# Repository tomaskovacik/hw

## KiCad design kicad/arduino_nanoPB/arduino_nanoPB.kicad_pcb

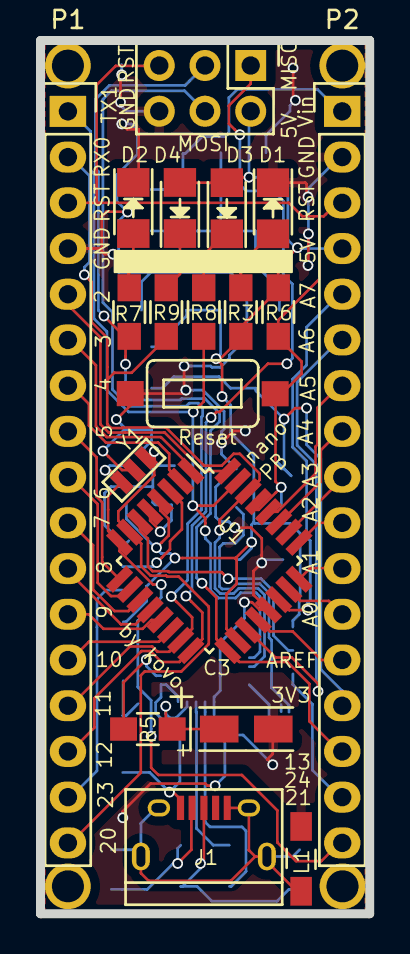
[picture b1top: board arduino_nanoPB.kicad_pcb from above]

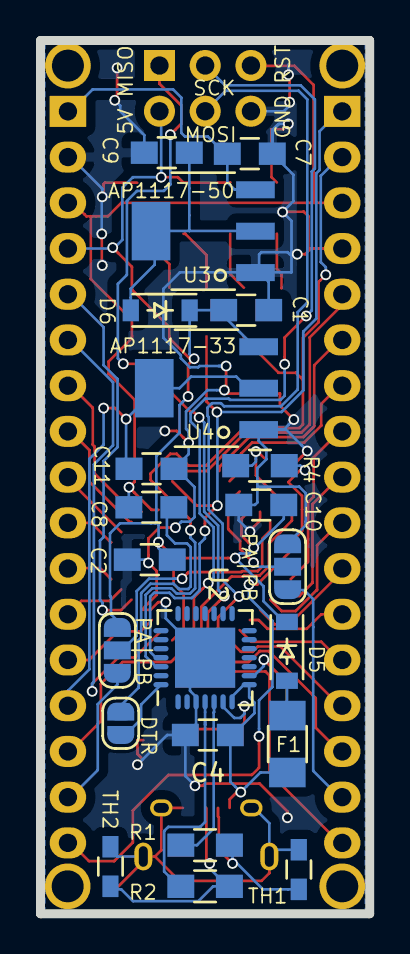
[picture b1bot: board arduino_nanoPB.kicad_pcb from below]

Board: 2 copper layers, 18.3 x 48.5 mm, 45 parts (22 on the bottom side), 50 nets.

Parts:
C1, C2, C4, C7, C8, C9, C10, C11: 0.1m; C_0805_HandSoldering
C3: 1u; TantalC_SizeA_EIA-3216_Wave
D1: Green RED; LED-1206
D2: Red LED; LED-1206
D3, D4: Yellow LED; LED-1206
D5, D6: MBR120; SOD-123
F1: Fuse; Fuse_SMD1206_Wave
J1: USB_B_Micro; USB_Micro-B
JP1, JP2: Jumper_3_Open; SolderJumper-3_P1.3mm_Open_RoundedPad1.0x1.5mm_NumberLabels
JP3: SolderJumper_2_Bridged; SolderJumper-2_P1.3mm_Open_RoundedPad1.0x1.5mm
L1: L; Choke_SMD_1206_Standard
P1: Digital; Pin_Header_Straight_1x17
P2: Analog; Pin_Header_Straight_1x17
P3, P4, P5, P6: CONN_01X01; 1pin_Nano
P7: CONN_6; Pin_Header_Straight_2x03
R1, R2: 20; R_0805_HandSoldering
R3, R7, R8, R9: 1k; R_0805_HandSoldering
R4: 1M; R_0805_HandSoldering
R5, R6: 10k; R_0805_HandSoldering
SW1: SW_PUSH; 3x6x2.5mm_tact_switch
TH1, TH2: CG0603MLC-05E; R_0603_HandSoldering
U1: ATMEGA328PB-AU; TQFP-32_7x7mm_Pitch0.8mm
U2: CP2102N-A01-GQFN28; QFN-28-1EP_5x5mm_Pitch0.5mm
U3: AP1117-50; AB2_SOT223
U4: AP1117-33; AB2_SOT223
Y1: Resonator; MURATA_CSTCE_V53

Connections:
3V3: C11.1, P2.14, U4.2
+5V: C1.2, C2.2, C10.1, D3.2, D4.2, D5.1, D6.1, JP2.3, P2.4, P7.2, R3.1, R6.1, U1.4, U1.18, U4.3
/0(Rx): P1.2, R9.1, U1.30, U2.26
/1(Tx): P1.1, R8.1, U1.31, U2.25
/2: P1.5, U1.32
/3(**): P1.6, U1.1
/4: P1.7, U1.2
/5(**): P1.8, U1.9
/6(**): P1.9, U1.10
/7: P1.10, U1.11
/8: P1.11, U1.12
/9(**): P1.12, U1.13
/10(**/SS): P1.13, U1.14
/11(**/MOSI): P1.14, P7.4, U1.15
/12(MISO): P1.15, P7.1, U1.16
/13(SCK): P2.15, P7.3, R7.1, U1.17
/20: P1.17, R4.1, U1.7, Y1.3
/21: P2.17, R4.2, U1.8, Y1.1
/#RST: R5.1, U2.9
/A0: P2.12, U1.23
/A1: P2.11, U1.24
/A2: P2.10, U1.25
/A3: P2.9, U1.26
/A4: P2.8, U1.27
/A5: P2.7, U1.28
/A6: P2.6, U1.19
/A7: P2.5, U1.22
/AREF: P2.13, U1.20
/D23: JP1.1, P1.16
/D24: JP2.1, P2.16
/D+: J1.3, R2.2, TH2.1
/D-: J1.2, R1.2, TH1.1
/DD+: R2.1, U2.4
/DD-: R1.1, U2.5
/DTR: JP3.2, U2.28
/MEGA3: JP1.2, U1.3
/MEGA6: JP2.2, U1.6
/Reset: C8.1, P1.3, P2.3, P7.5, R6.2, SW1.1, U1.29
/VBUS: C4.1, F1.2, J1.1, U2.7, U2.8
/Vin: C7.1, P2.1, U3.3
GND: C1.1, C2.1, C3.2, C4.2, C7.2, C9.2, C10.2, C11.2, D1.1, D2.1, JP1.3, L1.1, P1.4, P2.2, P7.6, SW1.2, U1.5, U1.21, U2.3, U2.29, U3.1, U4.1, Y1.2
GNDPWR: J1.5, J1.6, L1.2, TH1.2, TH2.2
unnamed: C3.1, R5.2, U2.6
unnamed: C8.2, JP3.1
unnamed: C9.1, D6.2, U3.2
unnamed: D1.2, R3.2
unnamed: D2.2, R7.2
unnamed: D3.1, R8.2
unnamed: D4.1, R9.2
unnamed: D5.2, F1.1

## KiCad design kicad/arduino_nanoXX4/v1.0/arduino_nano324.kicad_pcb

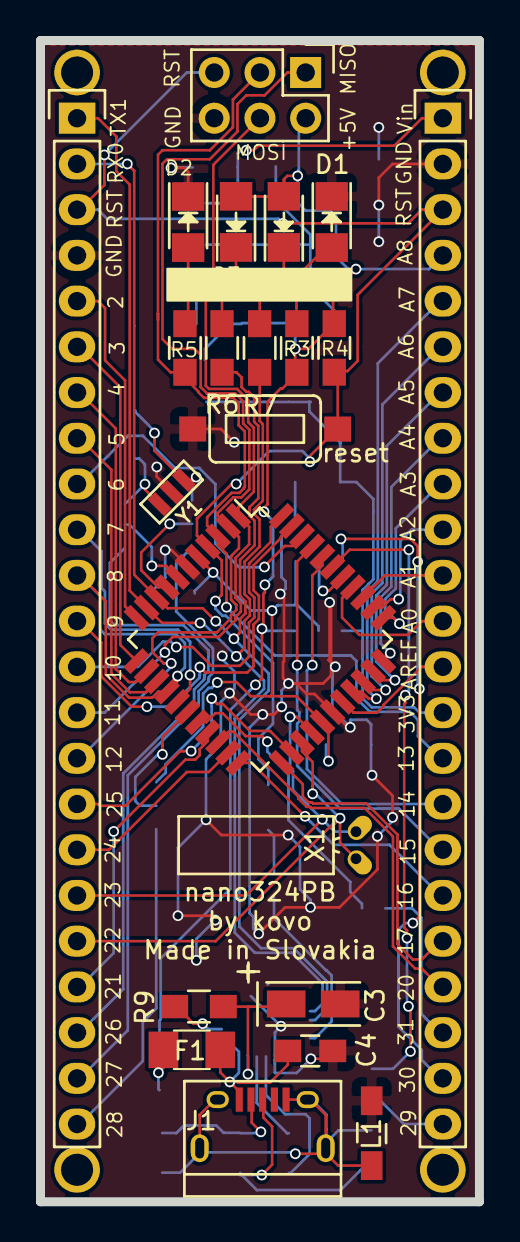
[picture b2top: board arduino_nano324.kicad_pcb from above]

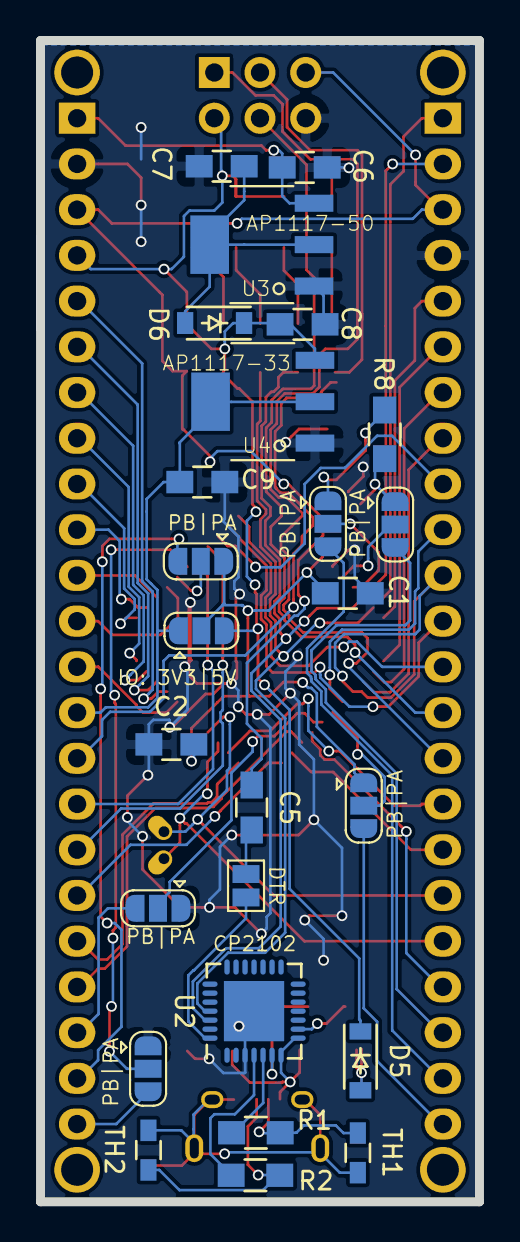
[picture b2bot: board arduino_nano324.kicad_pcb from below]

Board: 2 copper layers, 24.4 x 64.5 mm, 51 parts (25 on the bottom side), 69 nets.

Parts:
C1, C2, C4, C5, C6, C7, C8, C9: 0.1m; C_0805_HandSoldering
C3: 1u; TantalC_SizeA_EIA-3216_Wave
D1: GRED; LED-1206
D2: GLED; LED-1206
D3, D4: YLED; LED-1206
D5, D6: MBR120; SOD-123
F1: Fuse; Fuse_SMD1206_Wave
J1: USB_B_Micro; USB_Micro-B
JP1, JP2, JP3, JP4, JP5, JP6: Jumper_3_Open; SolderJumper-3_P1.3mm_Open_RoundedPad1.0x1.5mm
JP7: VIO; SolderJumper-3_P1.3mm_Open_RoundedPad1.0x1.5mm
JP9: Jumper; SolderJumper-2_P1.3mm_Open_Pad1.0x1.5mm
L1: ferite_bead; Choke_SMD_1206_Standard
P1: Digital; Pin_Header_Straight_1x23
P2: Analog; Pin_Header_Straight_1x23
P3, P4, P5, P6: CONN_01X01; 1pin_Nano
P7: CONN_6; Pin_Header_Straight_2x03
R1, R2: 22; R_0805_HandSoldering
R3, R5, R6, R7: 1k; R_0805_HandSoldering
R4, R9: 10k; R_0805_HandSoldering
R8: 1M; R_0805_HandSoldering
SW1: SW_PUSH; 3x6x2.5mm_tact_switch
TH1, TH2: MLC-05E; R_0603_HandSoldering
U1: ATMEGA324PB-AU; TQFP-44_10x10mm_Pitch0.8mm
U2: CP2102N-A01-GQFN28; QFN-28-1EP_5x5mm_Pitch0.5mm
U3: AP1117-50; AB2_SOT223
U4: AP1117-33; AB2_SOT223
X1: CRYSTAL; Crystal_Round_Horizontal_3mm_BigPad
Y1: 16Mhz; MURATA_CSTCE_V53

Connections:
3V3: C9.1, JP7.1, P2.14, U4.2
+5V: C8.1, D3.2, D4.2, D5.1, D6.1, JP7.3, P2.4, P7.2, R3.1, R4.1, U4.3
/0(Rx): P1.2, R6.1, U1.9, U2.26
/1(Tx): P1.1, R7.1, U1.10, U2.25
/2: P1.5, U1.11
/3(**): P1.6, U1.12
/4: P1.7, U1.13
/5(**): P1.8, U1.14
/6(**): P1.9, U1.42
/7: JP1.2, U1.7
/8: JP2.2, U1.8
/9(**): P1.12, U1.43
/10(**/SS): P1.13, U1.44
/11(**/MOSI): P1.14, P7.4, U1.1
/12(MISO): P1.15, P7.1, U1.2
/13(SCK): P2.15, P7.3, R5.1, U1.3
/17: JP3.2, U1.17
/18: JP4.2, U1.18
/38: JP5.2, U1.38
/39: JP6.2, U1.39
/#RST: R9.1, U2.9
/A0: P2.12, U1.37
/A1: P2.11, U1.36
/A2: P2.10, U1.35
/A3: P2.9, U1.34
/A4: P2.8, U1.33
/A5: P2.7, U1.32
/A6: P2.6, U1.31
/A7: P2.5, U1.30
/AREF: P2.13, U1.29
/D7: P1.10, U1.16
/D8: P1.11, U1.15
/D14: P2.16, U1.40
/D15: P2.17, U1.41
/D16: P2.18, U1.22
/D17: P2.19, U1.23
/D20: P2.20, U1.20
/D21: P1.20, U1.19
/D22: P1.19, U1.25, X1.1
/D23: P1.18, U1.26, X1.2
/D32: P1.17, U1.21
/D33: P1.16, U1.24
/D34: JP1.3, P1.21
/D35: JP2.3, P1.22
/D36: JP3.3, P1.23
/D37: JP4.3, P2.21
/D39: JP5.3, P2.22
/D40: JP6.3, P2.23
/D+: J1.3, R2.2, TH2.1
/D-: J1.2, R1.2, TH1.1
/DD+: R2.1, U2.4
/DD-: R1.1, U2.5
/DTR: JP9.2, U2.28
/Reset: C5.1, P1.3, P2.3, P7.5, R4.2, SW1.1, U1.4
/VBUS: C4.1, F1.2, J1.1, U2.7, U2.8
/Vin: C6.1, P2.1, U3.3
/XTAL1: JP2.1, R8.1, Y1.3
/XTAL2: JP1.1, R8.2, Y1.1
GND: C1.1, C2.1, C3.2, C4.2, C6.2, C7.2, C8.2, C9.2, D1.1, D2.1, JP4.1, JP6.1, L1.1, P1.4, P2.2, P7.6, SW1.2, U1.6, U1.28, U2.3, U2.29, U3.1, U4.1, Y1.2
GNDPWR: J1.5, J1.6, L1.2, TH1.2, TH2.2
unnamed: C3.1, R9.2, U2.6
unnamed: C5.2, JP9.1
unnamed: C7.1, D6.2, U3.2
unnamed: D1.2, R3.2
unnamed: D2.2, R5.2
unnamed: D3.1, R6.2
unnamed: D4.1, R7.2
unnamed: D5.2, F1.1
VCC: C1.2, C2.2, JP3.1, JP5.1, JP7.2, U1.5, U1.27

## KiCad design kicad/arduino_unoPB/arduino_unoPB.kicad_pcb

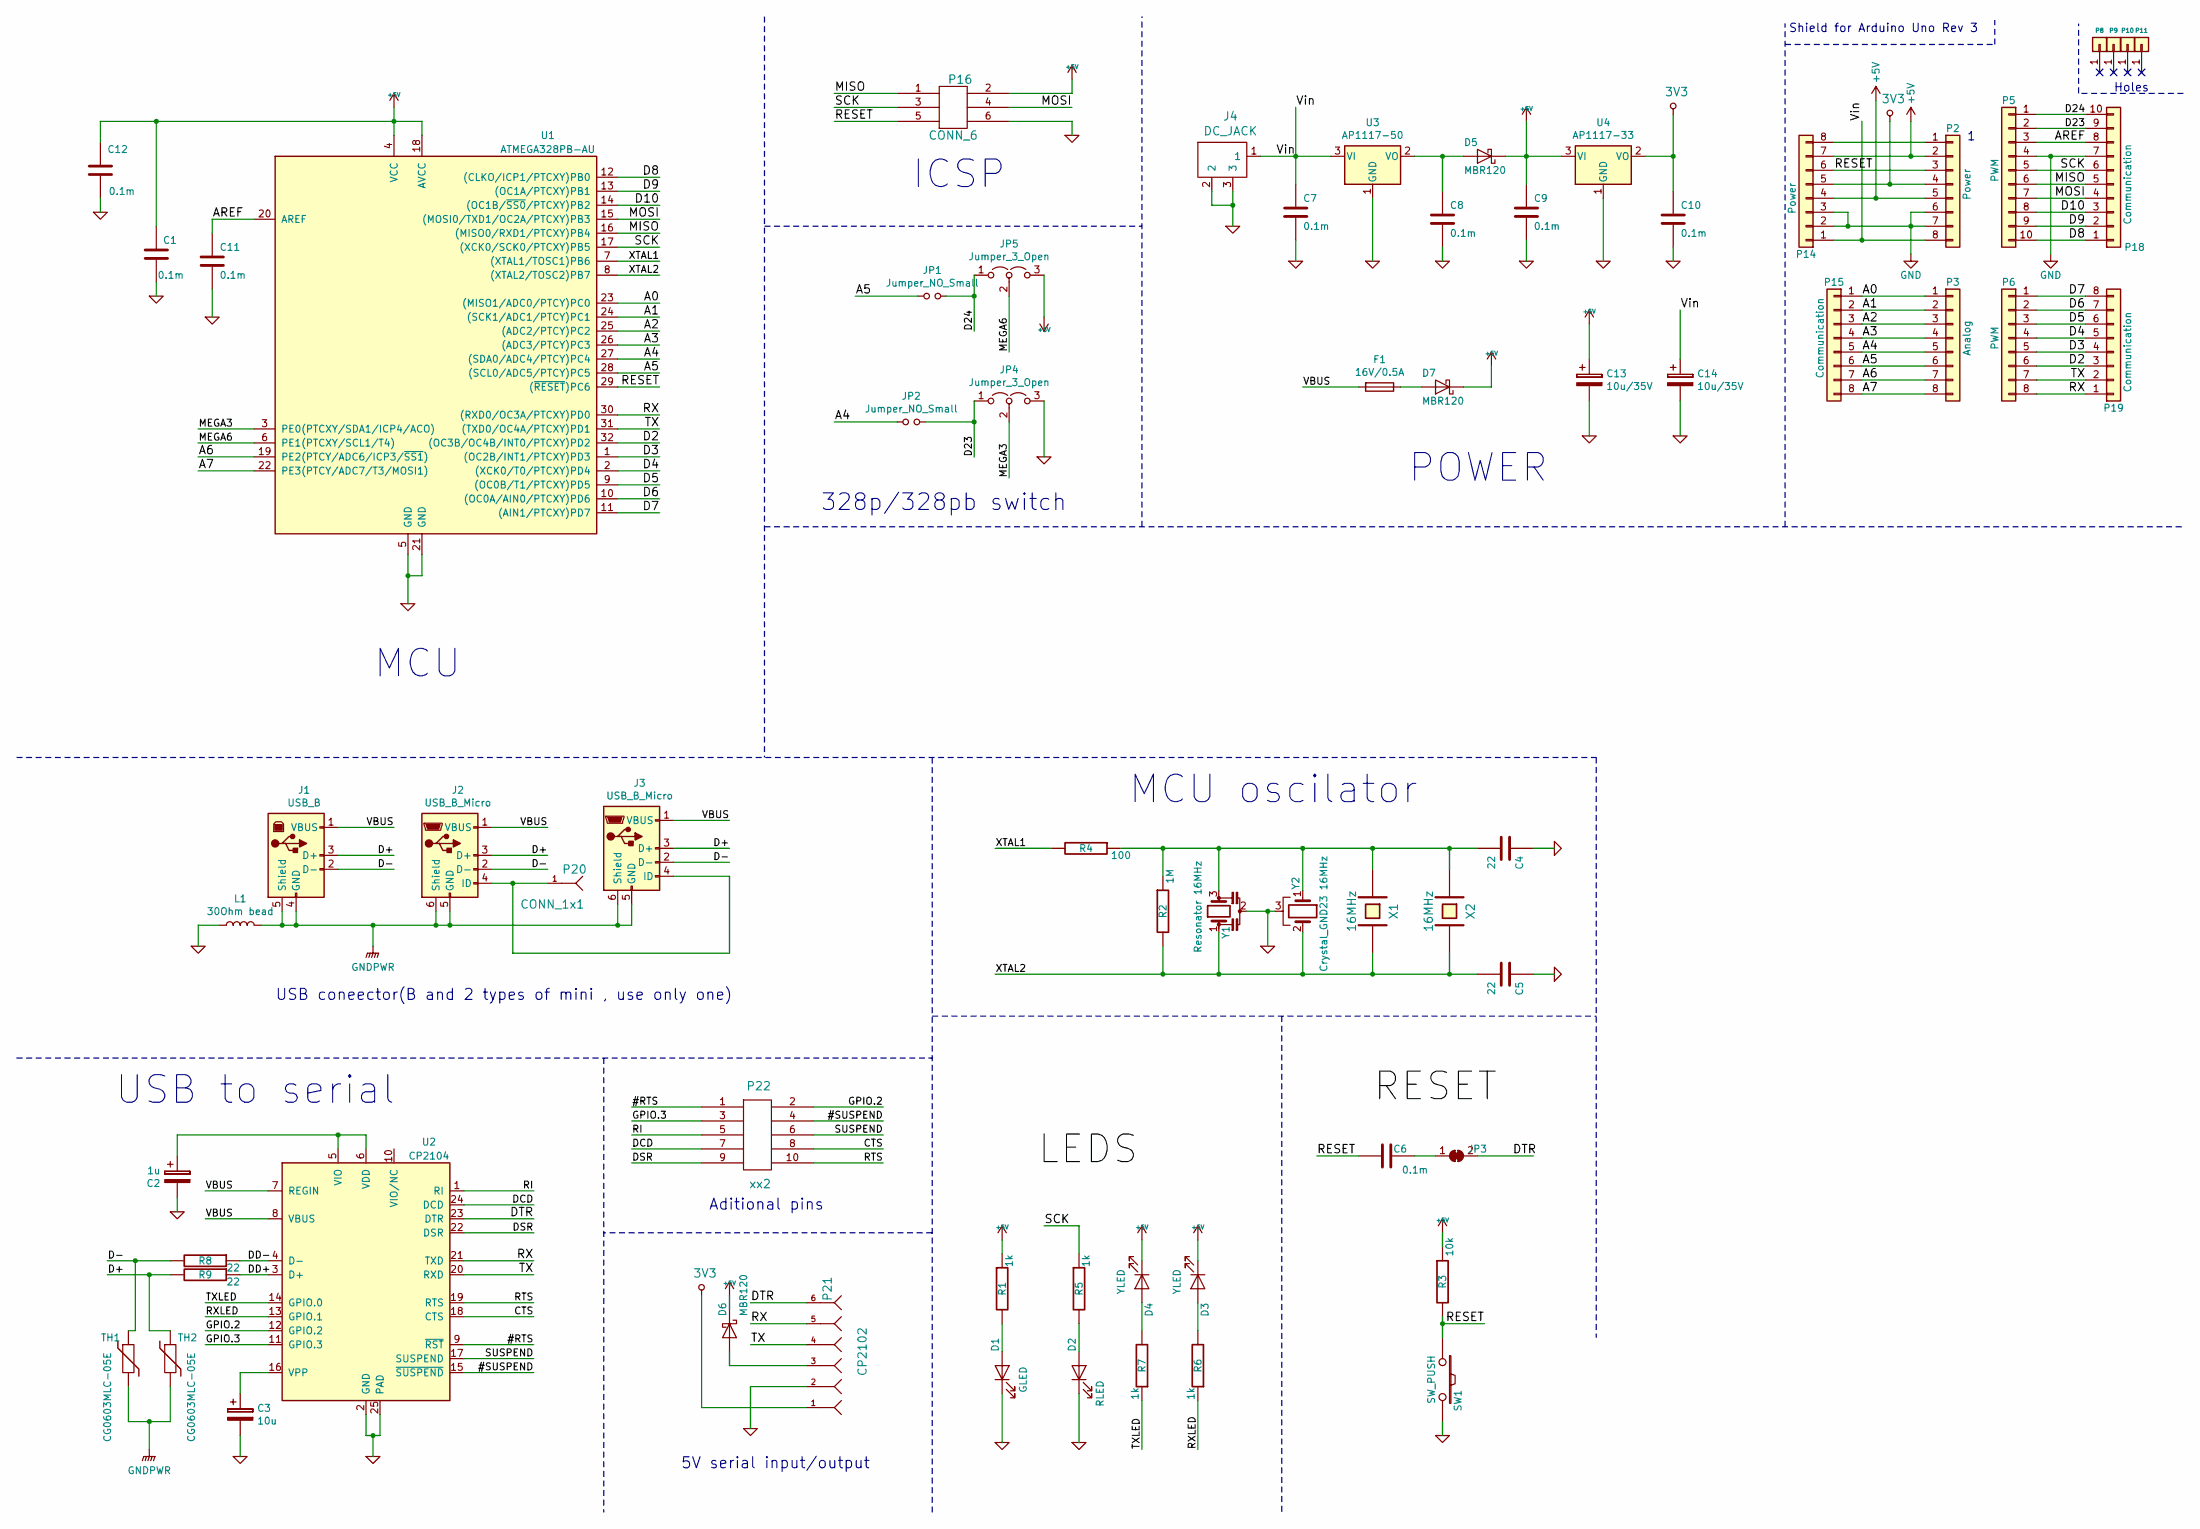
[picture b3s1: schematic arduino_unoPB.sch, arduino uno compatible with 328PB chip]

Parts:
C1, C6, C7, C8, C9, C10, C11, C12: 0.1m; C_0805_HandSoldering
C2: 1u; TantalC_SizeA_EIA-3216_Wave
C3: 10u; TantalC_SizeA_EIA-3216_Wave
C4, C5: 22; C_0805_HandSoldering
C13, C14: 10u/35V; TantalC_SizeD_EIA-7343_Wave
D1: GLED; LED-1206
D2: RLED; LED-1206
D3, D4: YLED; LED-1206
D5, D6, D7: MBR120; SOD-123
F1: 16V/0.5A; Fuse_SMD1206_Wave
J1: USB_B
J2: USB_B_Micro; USB_Micro-B
J3: USB_B_Micro; AB2_USB_MICRO_SMD
J4: DC_JACK; JACK_ALIM
JP1, JP2: Jumper_NO_Small; SolderJumper-2_P1.3mm_Open_RoundedPad1.0x1.5mm
JP3: SolderJumper_2_Bridged; SolderJumper-2_P1.3mm_Bridged_RoundedPad1.0x1.5mm
JP4, JP5: Jumper_3_Open; SolderJumper-3_P1.3mm_Open_RoundedPad1.0x1.5mm_NumberLabels
L1: 30Ohm bead; Choke_SMD_1206_Standard
P2, P14: Power; Pin_Header_Straight_1x08
P3: Analog; Pin_Header_Straight_1x08
P5: PWM; Pin_Header_Straight_1x10
P6: PWM; Pin_Header_Straight_1x08
P8, P9, P10, P11: CONN_01X01; Arduino_1pin
P15, P19: Communication; Pin_Header_Straight_1x08
P16: CONN_6; Pin_Header_Straight_2x03
P18: Communication; Pin_Header_Straight_1x10
P20: CONN_1x1; Pin_Header_Straight_1x01
P21: CP2102; Pin_Header_Straight_1x06
P22: xx2; Pin_Header_Straight_2x05
R1, R5, R6, R7: 1k; R_0805_HandSoldering
R2: 1M; R_0805_HandSoldering
R3: 10k; R_0805_HandSoldering
R4: 100; R_0805_HandSoldering
R8, R9: 22; R_0805_HandSoldering
SW1: SW_PUSH; 3x6x2.5mm_tact_switch
TH1, TH2: CG0603MLC-05E; R_0603_HandSoldering
U1: ATMEGA328PB-AU; TQFP-32_7x7mm_Pitch0.8mm
U2: CP2104; QFN-24-1EP_4x4mm_Pitch0.5mm
U3: AP1117-50; AB2_SOT223
U4: AP1117-33; AB2_SOT223
X1: 16MHz; Crystal_HC49-U_Vertical
X2: 16MHz; Q_49U3HMS
Y1: Resonator 16MHz; MURATA_CSTCE_V53
Y2: Crystal_GND23 16MHz; CRYSTAL_3225

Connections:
3V3: C10.1, P2.4, P14.5, P21.1, U4.2 (VO)
+5V: C1.2, C9.1, C12.2, C13.1, D3.1 (K), D4.1 (K), D5.1 (K), D6.1 (K), D7.1 (K), JP5.3 (B), P2.2, P2.5, P14.4, P14.7, P16.2, R1.1, R3.1, U1.4 (VCC), U1.18 (AVCC), U4.3 (VI)
/#RTS: P22.1, U2.9 (~RST)
/#SUSPEND: P22.4, U2.15 (~SUSPEND)
/A0: P3.1, P15.1, U1.23 ((MISO1/ADC0/PTCY)PC0)
/A1: P3.2, P15.2, U1.24 ((SCK1/ADC1/PTCY)PC1)
/A2: P3.3, P15.3, U1.25 ((ADC2/PTCY)PC2)
/A3: P3.4, P15.4, U1.26 ((ADC3/PTCY)PC3)
/A4: JP2.1, P3.5, P15.5, U1.27 ((SDA0/ADC4/PTCY)PC4)
/A5: JP1.1, P3.6, P15.6, U1.28 ((SCL0/ADC5/PTCY)PC5)
/A6: P3.7, P15.7, U1.19 (PE2(PTCY/ADC6/ICP3/~SS1~))
/A7: P3.8, P15.8, U1.22 (PE3(PTCY/ADC7/T3/MOSI1))
/AREF: C11.1, P5.3, P18.8, U1.20 (AREF)
/CTS: P22.8, U2.18 (CTS)
/D2: P6.6, P19.3, U1.32 ((OC3B/OC4B/INT0/PTCXY)PD2)
/D3: P6.5, P19.4, U1.1 ((OC2B/INT1/PTCXY)PD3)
/D4: P6.4, P19.5, U1.2 ((XCK0/T0/PTCXY)PD4)
/D5: P6.3, P19.6, U1.9 ((OC0B/T1/PTCXY)PD5)
/D6: P6.2, P19.7, U1.10 ((OC0A/AIN0/PTCXY)PD6)
/D7: P6.1, P19.8, U1.11 ((AIN1/PTCXY)PD7)
/D8: P5.10, P18.1, U1.12 ((CLKO/ICP1/PTCXY)PB0)
/D9: P5.9, P18.2, U1.13 ((OC1A/PTCXY)PB1)
/D10: P5.8, P18.3, U1.14 ((OC1B/~SS0~/PTCXY)PB2)
/D23: JP2.2, JP4.1 (A), P5.2, P18.9
/D24: JP1.2, JP5.1 (A), P5.1, P18.10
/D+: J1.3 (D+), J2.3 (D+), J3.3 (D+), R9.2, TH2.1
/D-: J1.2 (D-), J2.2 (D-), J3.2 (D-), R8.2, TH1.1
/DCD: P22.7, U2.24 (DCD)
/DD+: R9.1, U2.3 (D+)
/DD-: R8.1, U2.4 (D-)
/DSR: P22.9, U2.22 (DSR)
/DTR: JP3.2 (B), P21.6, U2.23 (DTR)
/GPIO.2: P22.2, U2.12 (GPIO.2)
/GPIO.3: P22.3, U2.11 (GPIO.3)
/MEGA3: JP4.2 (C), U1.3 (PE0(PTCXY/SDA1/ICP4/ACO))
/MEGA6: JP5.2 (C), U1.6 (PE1(PTCXY/SCL1/T4))
/MISO: P5.6, P16.1, P18.5, U1.16 ((MISO0/RXD1/PTCXY)PB4)
/MOSI: P5.7, P16.4, P18.4, U1.15 ((MOSI0/TXD1/OC2A/PTCXY)PB3)
/RESET: C6.1, P2.3, P14.6, P16.5, R3.2, SW1.1, U1.29 ((~RESET~)PC6)
/RI: P22.5, U2.1 (RI)
/RTS: P22.10, U2.19 (RTS)
/RX: P6.8, P19.1, P21.5, U1.30 ((RXD0/OC3A/PTCXY)PD0), U2.21 (TXD)
/RXLED: R6.1, U2.13 (GPIO.1)
/SCK: P5.5, P16.3, P18.6, R5.1, U1.17 ((XCK0/SCK0/PTCXY)PB5)
/SUSPEND: P22.6, U2.17 (SUSPEND)
/TX: P6.7, P19.2, P21.4, U1.31 ((TXD0/OC4A/PTCXY)PD1), U2.20 (RXD)
/TXLED: R7.1, U2.14 (GPIO.0)
/VBUS: F1.2, J1.1 (VBUS), J2.1 (VBUS), J3.1 (VBUS), U2.7 (REGIN), U2.8 (VBUS)
/Vin: C7.1, C14.1, J4.1, P2.8, P14.1, U3.3 (VI)
/XTAL1: R4.2, U1.7 ((XTAL1/TOSC1)PB6)
/XTAL2: C5.2, R2.2, U1.8 ((XTAL2/TOSC2)PB7), X1.2, X2.2, Y1.1, Y2.2
GND: C1.1, C2.2, C3.2, C4.1, C5.1, C7.2, C8.2, C9.2, C10.2, C11.2, C12.1, C13.2, C14.2, D1.1 (K), D2.1 (K), J4.2, J4.3, JP4.3 (B), L1.1, P2.6, P2.7, P5.4, P14.2, P14.3, P16.6, P18.7, P21.2, SW1.2, U1.5 (GND), U1.21 (GND), U2.2 (GND), U2.25 (PAD), U3.1 (GND), U4.1 (GND), Y1.2, Y2.3
GNDPWR: J1.4 (GND), J1.5 (Shield), J2.5 (GND), J2.6 (Shield), J3.5 (GND), J3.6 (Shield), L1.2, TH1.2, TH2.2
unnamed: C2.1, U2.5 (VIO), U2.6 (VDD)
unnamed: C3.1, U2.16 (VPP)
unnamed: C4.2, R2.1, R4.1, X1.1, X2.1, Y1.3, Y2.1
unnamed: C6.2, JP3.1 (A)
unnamed: C8.1, D5.2 (A), U3.2 (VO)
unnamed: D1.2 (A), R1.2
unnamed: D2.2 (A), R5.2
unnamed: D3.2 (A), R6.2
unnamed: D4.2 (A), R7.2
unnamed: D6.2 (A), P21.3
unnamed: D7.2 (A), F1.1
unnamed: J2.4 (ID), J3.4 (ID), P20.1
unnamed: P2.1, P14.8

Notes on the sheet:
328p/328pb switch
ICSP
MCU oscilator
MCU
USB to serial
USB coneector(B and 2 types of mini , use only one)
5V serial input/output
Aditional pins
Holes
Shield for Arduino Uno Rev 3
POWER

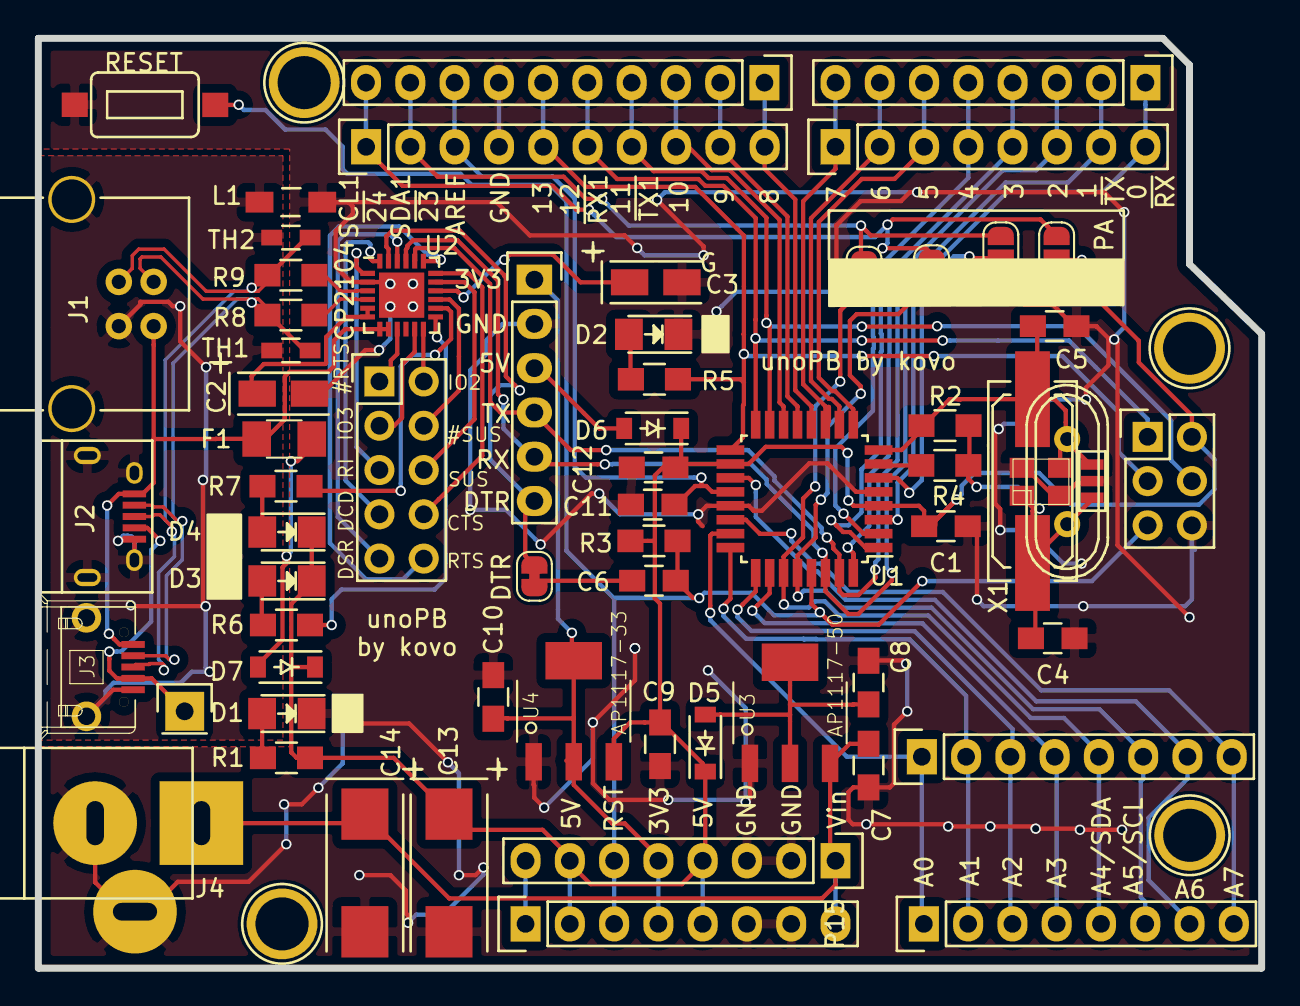
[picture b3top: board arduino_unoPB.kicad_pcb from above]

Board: 2 copper layers, 70.2 x 53.3 mm, 68 parts (0 on the bottom side), 66 nets.

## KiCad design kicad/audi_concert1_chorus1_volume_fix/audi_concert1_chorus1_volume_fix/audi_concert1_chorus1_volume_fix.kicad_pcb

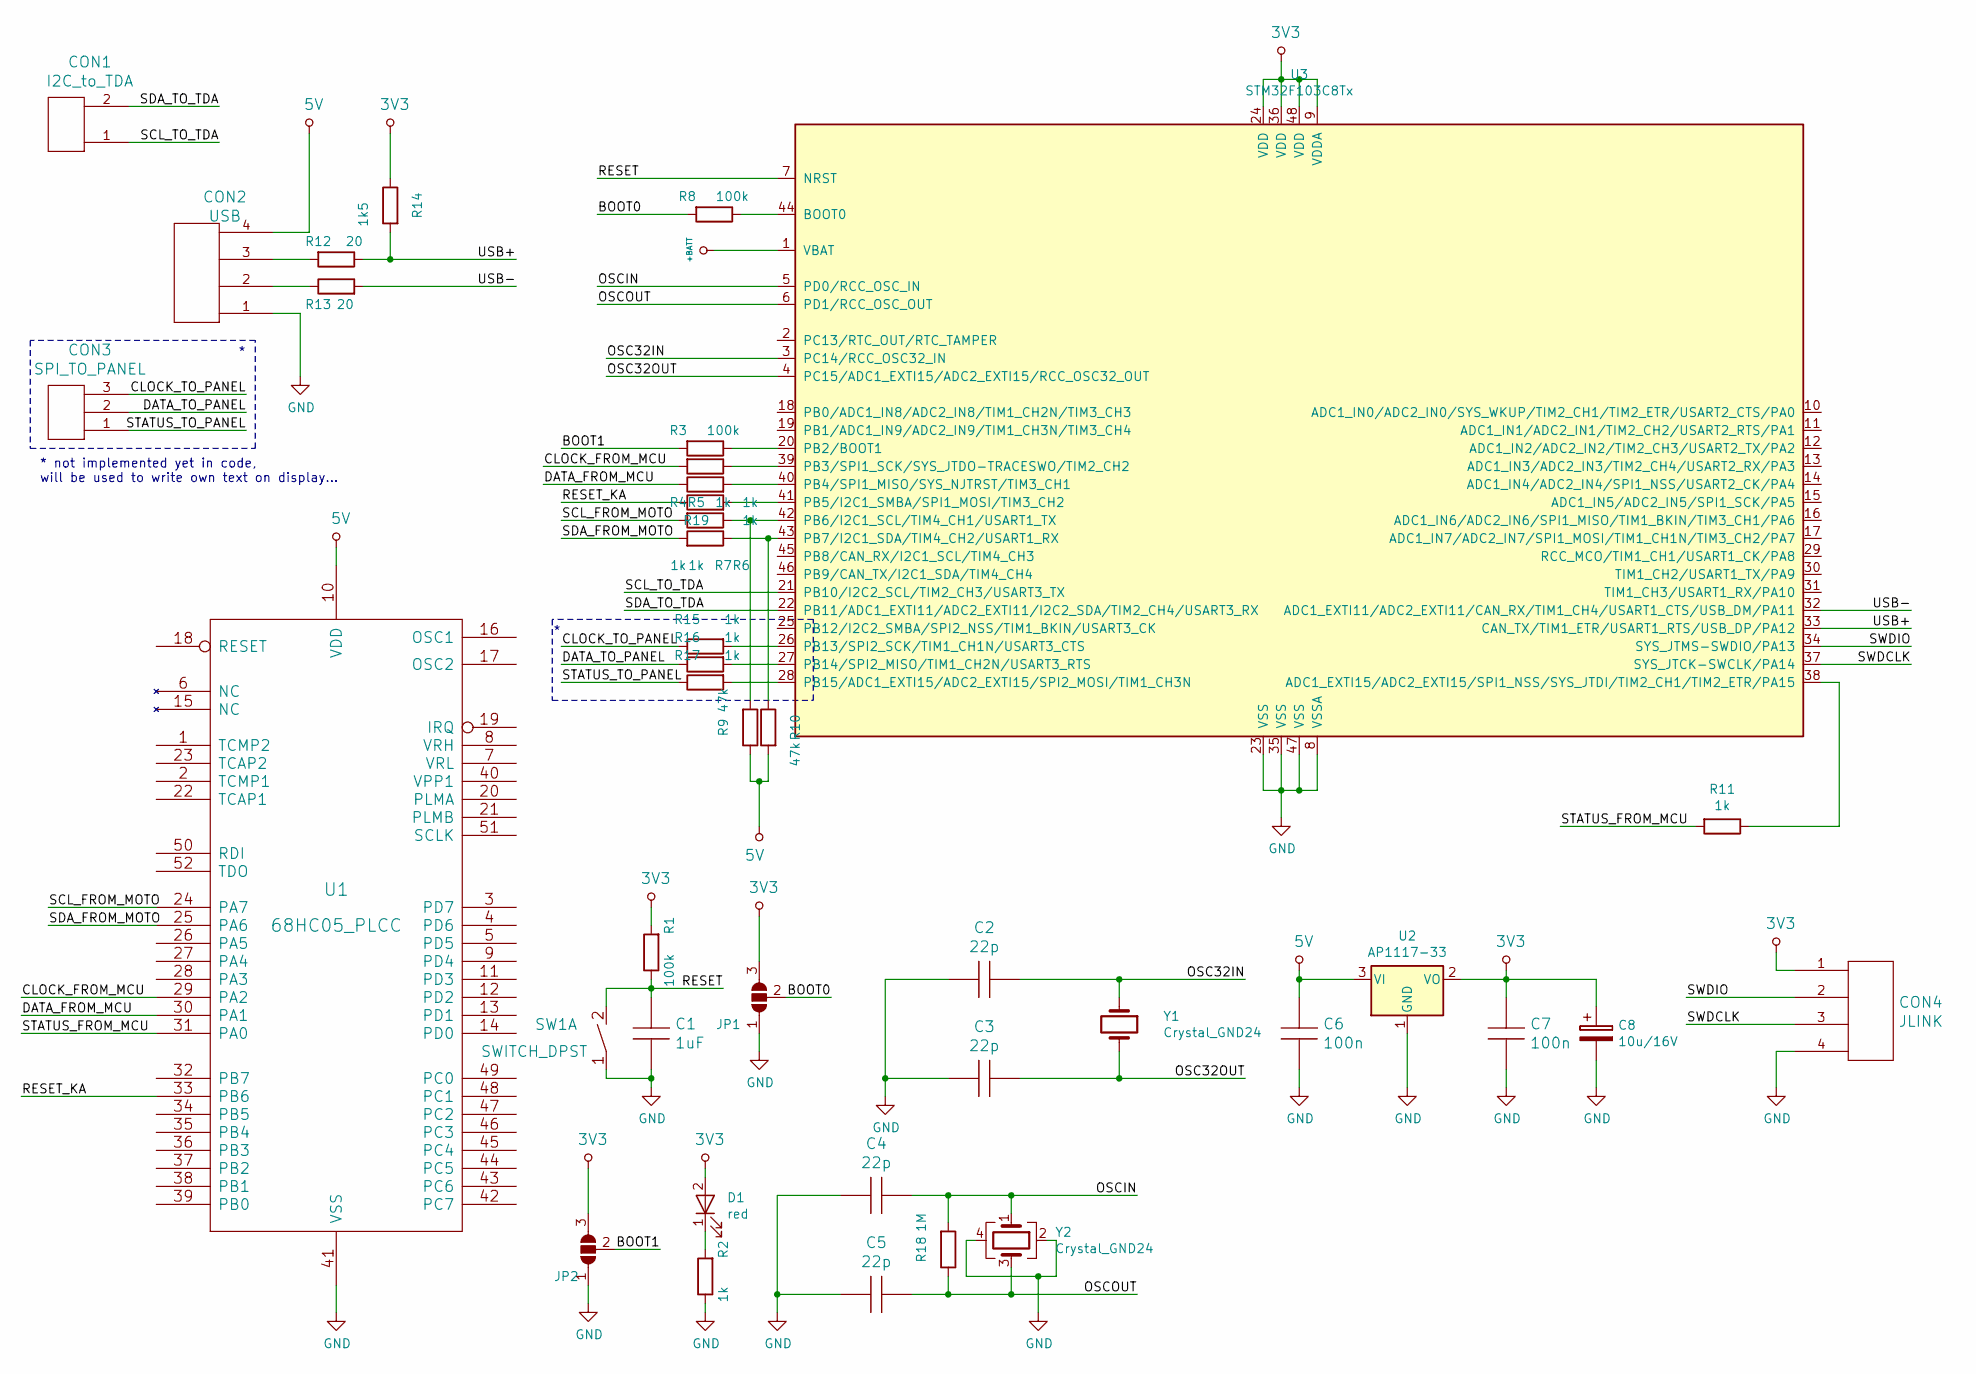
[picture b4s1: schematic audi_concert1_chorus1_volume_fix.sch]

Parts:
C1: 1uF; C_1206_HandSoldering
C2, C3, C4, C5: 22p; C_0805_HandSoldering
C6, C7: 100n; C_0805_HandSoldering
C8: 10u/16V; TantalC_SizeA_EIA-3216_HandSoldering
CON1: I2C_to_TDA; Pin_Header_Straight_1x02
CON2: USB; Pin_Header_Straight_1x04
CON3: SPI_TO_PANEL; Pin_Header_Straight_1x03
CON4: JLINK; Pin_Header_Straight_1x04
D1: red; LED-1206
JP1, JP2: SolderJumper_3_Open; SolderJumper-3_P1.3mm_Open_RoundedPad1.0x1.5mm_NumberLabels
R1, R3, R8: 100k; R_0805_HandSoldering
R2, R4, R5, R6, R7, R11, R15, R16, R17, R19: 1k; R_0805_HandSoldering
R9, R10: 47k; R_0805_HandSoldering
R12, R13: 20; R_0805_HandSoldering
R14: 1k5; R_0805_HandSoldering
R18: 1M; R_0805_HandSoldering
SW1: SWITCH_DPST; 3x6x2.5mm_tact_switch
U1: 68HC05_PLCC; PLCC-52_mirrored
U2: AP1117-33; AB2_SOT223
U3: STM32F103C8Tx; LQFP-48_7x7mm_Pitch0.5mm
Y1: Crystal_GND24; Crystal_SMD_3215-2pin_3.2x1.5mm
Y2: Crystal_GND24; Crystal_SMD_5032-4pin_5.0x3.2mm

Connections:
3V3: C7.1, C8.1, CON4.1, D1.2 (A), JP1.3 (B), JP2.3 (B), R1.2, R14.1, U2.2 (VO), U3.9 (VDDA), U3.24 (VDD), U3.36 (VDD), U3.48 (VDD)
5V: C6.1, CON2.4, R9.1, R10.2, U1.10 (VDD), U2.3 (VI)
+BATT: U3.1 (VBAT)
/BOOT0: JP1.2 (C), R8.2
/BOOT1: JP2.2 (C), R3.2
/CLOCK_FROM_MCU: R4.2, U1.29 (PA2)
/CLOCK_TO_PANEL: CON3.3, R15.1
/DATA_FROM_MCU: R5.1, U1.30 (PA1)
/DATA_TO_PANEL: CON3.2, R16.1
/OSC32IN: C2.1, U3.3 (PC14/RCC_OSC32_IN), Y1.1
/OSC32OUT: C3.2, U3.4 (PC15/ADC1_EXTI15/ADC2_EXTI15/RCC_OSC32_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), Y1.2
/OSCIN: C4.1, R18.2, U3.5 (PD0/RCC_OSC_IN), Y2.1
/OSCOUT: C5.2, R18.1, U3.6 (PD1/RCC_OSC_OUT), Y2.3
/RESET: C1.1, R1.1, SW1.2, U3.7 (NRST)
/RESET_KA: R19.1, U1.33 (PB6)
/SCL_FROM_MOTO: R6.2, U1.24 (PA7)
/SCL_TO_TDA: CON1.1, U3.21 (PB10/I2C2_SCL/TIM2_CH3/USART3_TX)
/SDA_FROM_MOTO: R7.2, U1.25 (PA6)
/SDA_TO_TDA: CON1.2, U3.22 (PB11/ADC1_EXTI11/ADC2_EXTI11/I2C2_SDA/T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)
/STATUS_FROM_MCU: R11.2, U1.31 (PA0)
/STATUS_TO_PANEL: CON3.1, R17.1
/SWDCLK: CON4.3, U3.37 (SYS_JTCK-SWCLK/PA14)
/SWDIO: CON4.2, U3.34 (SYS_JTMS-SWDIO/PA13)
/USB+: R12.1, R14.2, U3.33 (CAN_TX/TIM1_ETR/USART1_RTS/USB_DP/PA12)
/USB-: R13.2, U3.32 (ADC1_EXTI11/ADC2_EXTI11/CAN_RX/TIM1_CH4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)
GND: C1.2, C2.2, C3.1, C4.2, C5.1, C6.2, C7.2, C8.2, CON2.1, CON4.4, JP1.1 (A), JP2.1 (A), R2.1, SW1.1, U1.41 (VSS), U2.1 (GND), U3.8 (VSSA), U3.23 (VSS), U3.35 (VSS), U3.47 (VSS), Y2.2, Y2.4
unnamed: CON2.2, R13.1
unnamed: CON2.3, R12.2
unnamed: D1.1 (K), R2.2
unnamed: R3.1, U3.20 (PB2/BOOT1)
unnamed: R4.1, U3.39 (PB3/SPI1_SCK/SYS_JTDO-TRACESWO/TIM2_CH2)
unnamed: R5.2, U3.40 (PB4/SPI1_MISO/SYS_NJTRST/TIM3_CH1)
unnamed: R6.1, R9.2, U3.42 (PB6/I2C1_SCL/TIM4_CH1/USART1_TX)
unnamed: R8.1, U3.44 (BOOT0)
unnamed: R7.1, R10.1, U3.43 (PB7/I2C1_SDA/TIM4_CH2/USART1_RX)
unnamed: R11.1, U3.38 (ADC1_EXTI15/ADC2_EXTI15/SPI1_NSS/SYS_JT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)
unnamed: R15.2, U3.26 (PB13/SPI2_SCK/TIM1_CH1N/USART3_CTS)
unnamed: R16.2, U3.27 (PB14/SPI2_MISO/TIM1_CH2N/USART3_RTS)
unnamed: R17.2, U3.28 (PB15/ADC1_EXTI15/ADC2_EXTI15/SPI2_MOSI/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)
unnamed: R19.2, U3.41 (PB5/I2C1_SMBA/SPI1_MOSI/TIM3_CH2)

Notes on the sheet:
* not implemented yet in code, will be used to write own text on display...

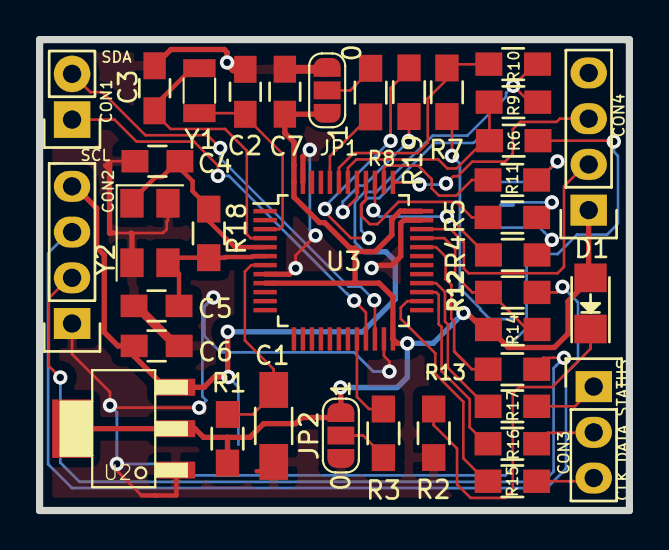
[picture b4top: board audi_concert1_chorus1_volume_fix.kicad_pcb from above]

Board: 2 copper layers, 32.8 x 26.2 mm, 38 parts (0 on the bottom side), 39 nets.

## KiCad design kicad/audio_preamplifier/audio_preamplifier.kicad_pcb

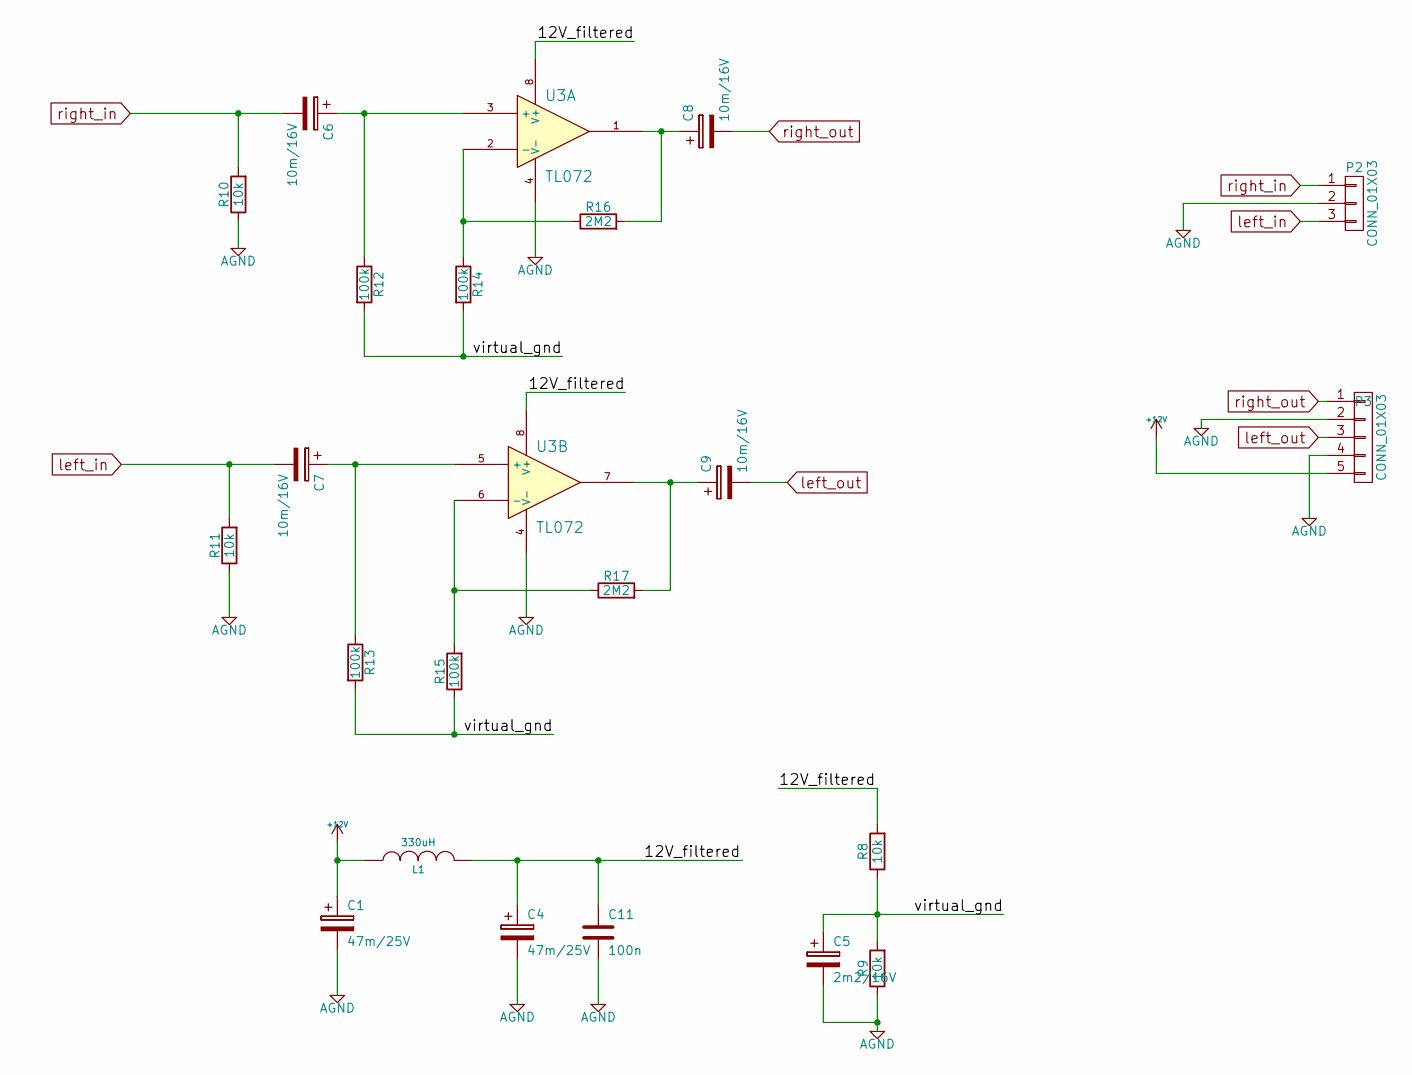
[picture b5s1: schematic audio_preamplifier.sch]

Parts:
C1, C4: 47m/25V; CP_Tantalum_Case-D_EIA-7343-31_Hand
C5: 2m2/16V; TantalC_SizeA_EIA-3216_HandSoldering
C6, C7, C8, C9: 10m/16V; CP_Elec_5x5.8
C11: 100n; C_0805_HandSoldering
L1: 330uH; Inductor_1212
P2: CONN_01X03; Pin_Header_Straight_1x03_Pitch2.54mm
P3: CONN_01X03; Pin_Header_Straight_1x05_Pitch2.54mm
R8, R9, R10, R11: 10k; R_0805_HandSoldering
R12, R13, R14, R15: 100k; R_0805_HandSoldering
R16, R17: 2M2; R_0805_HandSoldering
U3: TL072; SOIC-8_3.9x4.9mm_Pitch1.27mm

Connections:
+12V: C1.1, L1.1, P3.5
/12V_filtered: C4.1, C11.1, L1.2, R8.2, U3.8 (V+)
/virtual_gnd: C5.1, R8.1, R9.2, R12.2, R13.2, R14.2, R15.1
AGND: C1.2, C4.2, C5.2, C11.2, P2.2, P3.2, P3.4, R9.1, R10.1, R11.1, U3.4 (V-)
unnamed: C6.1, R12.1, U3.3 (+)
unnamed: C7.1, R13.1, U3.5 (+)
unnamed: C8.1, R16.2, U3.1
unnamed: C9.1, R17.2, U3.7
unnamed: R14.1, R16.1, U3.2 (-)
unnamed: R15.2, R17.1, U3.6 (-)
left_in: C7.2, P2.3, R11.2
left_out: C9.2, P3.3
right_in: C6.2, P2.1, R10.2
right_out: C8.2, P3.1

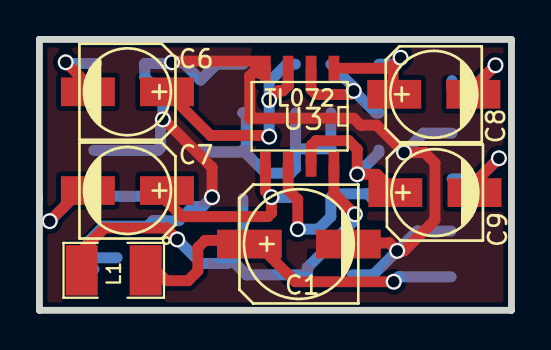
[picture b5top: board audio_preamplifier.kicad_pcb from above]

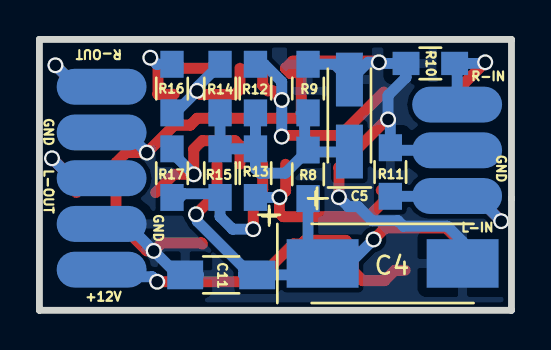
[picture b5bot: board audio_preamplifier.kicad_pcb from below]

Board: 2 copper layers, 26.2 x 15.0 mm, 22 parts (13 on the bottom side), 14 nets.
